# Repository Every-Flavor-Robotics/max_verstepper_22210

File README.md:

# max_verstepper_22210 (WIP)
This is a breakoutboard for the Trinamic MAX22210 motor driver ic

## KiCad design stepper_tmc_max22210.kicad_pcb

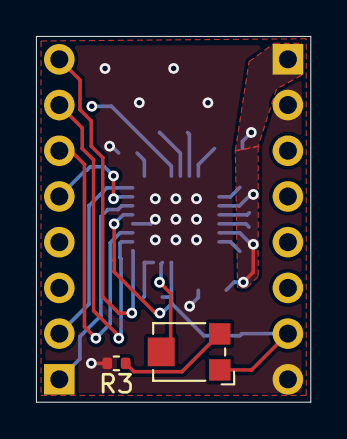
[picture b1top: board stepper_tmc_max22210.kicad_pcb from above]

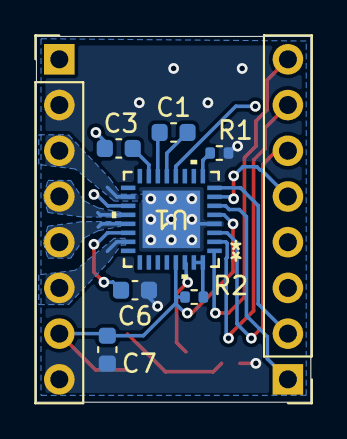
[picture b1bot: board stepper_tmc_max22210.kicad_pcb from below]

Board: 4 copper layers, 15.2 x 20.3 mm, 11 parts (9 on the bottom side), 21 nets.

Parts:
50k1: rot_pot; Potentiometer_Bourns_TC33X_Vertical
C1: 22nF; C_0603_1608Metric
C3, C7: 1uf; C_0603_1608Metric
C6: 1uF; C_0603_1608Metric
J1, J2: Conn_01x08_pin; PinHeader_1x08_P2.54mm_Vertical
R1, R2: 10k; R_0402_1005Metric
R3: 12k; R_0402_1005Metric
U1: MAX22210ATJ+; 21-0140_T3255-8C_ADI

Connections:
DIR: J1.1, U1.6 (DIR)
EN: J1.8, U1.1 (EN)
GND: C6.1, C7.2, J2.2, J2.8, R1.2, R3.2, U1.4 (AGND), U1.33 (EPAD)
M1: J2.4, U1.20 (OUT2B)
M2: J2.3, U1.18 (OUT1B)
M3: J2.5, U1.21 (OUT2A)
M4: J2.6, U1.23 (OUT1A)
MODE0: J1.7, U1.2 (MODE0)
MODE1: J1.6, U1.3 (MODE1)
MODE2: J1.5, U1.7 (MODE2)
unnamed: 50k1.3, R3.1
unnamed: C1.2, U1.14 (CP1)
unnamed: C1.1, U1.13 (CP2)
unnamed: R2.2, U1.31 (DECAY2), U1.32 (DECAY1)
unnamed: 50k1.2, U1.30 (REF)
unnamed: C3.1, U1.15 (VCP)
SLEEP: J1.3, J1.4, U1.12 (SLEEP)
STEP: J1.2, U1.8 (STEP)
VDD: 50k1.1, C7.1, J2.7, R2.1, U1.5 (VDD), U1.29 (ROFF)
VMOT: C3.2, C6.2, J2.1, U1.19 (VM), U1.22 (VM)
hfs_select: R1.1, U1.9 (HFS)

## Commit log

2024-07-14 added project files
2024-07-15 finished schematic, started layout
2024-07-16 Finished functional design, ready for silk screen and BOM revision
2024-07-16 small pcb adjustments for photos
